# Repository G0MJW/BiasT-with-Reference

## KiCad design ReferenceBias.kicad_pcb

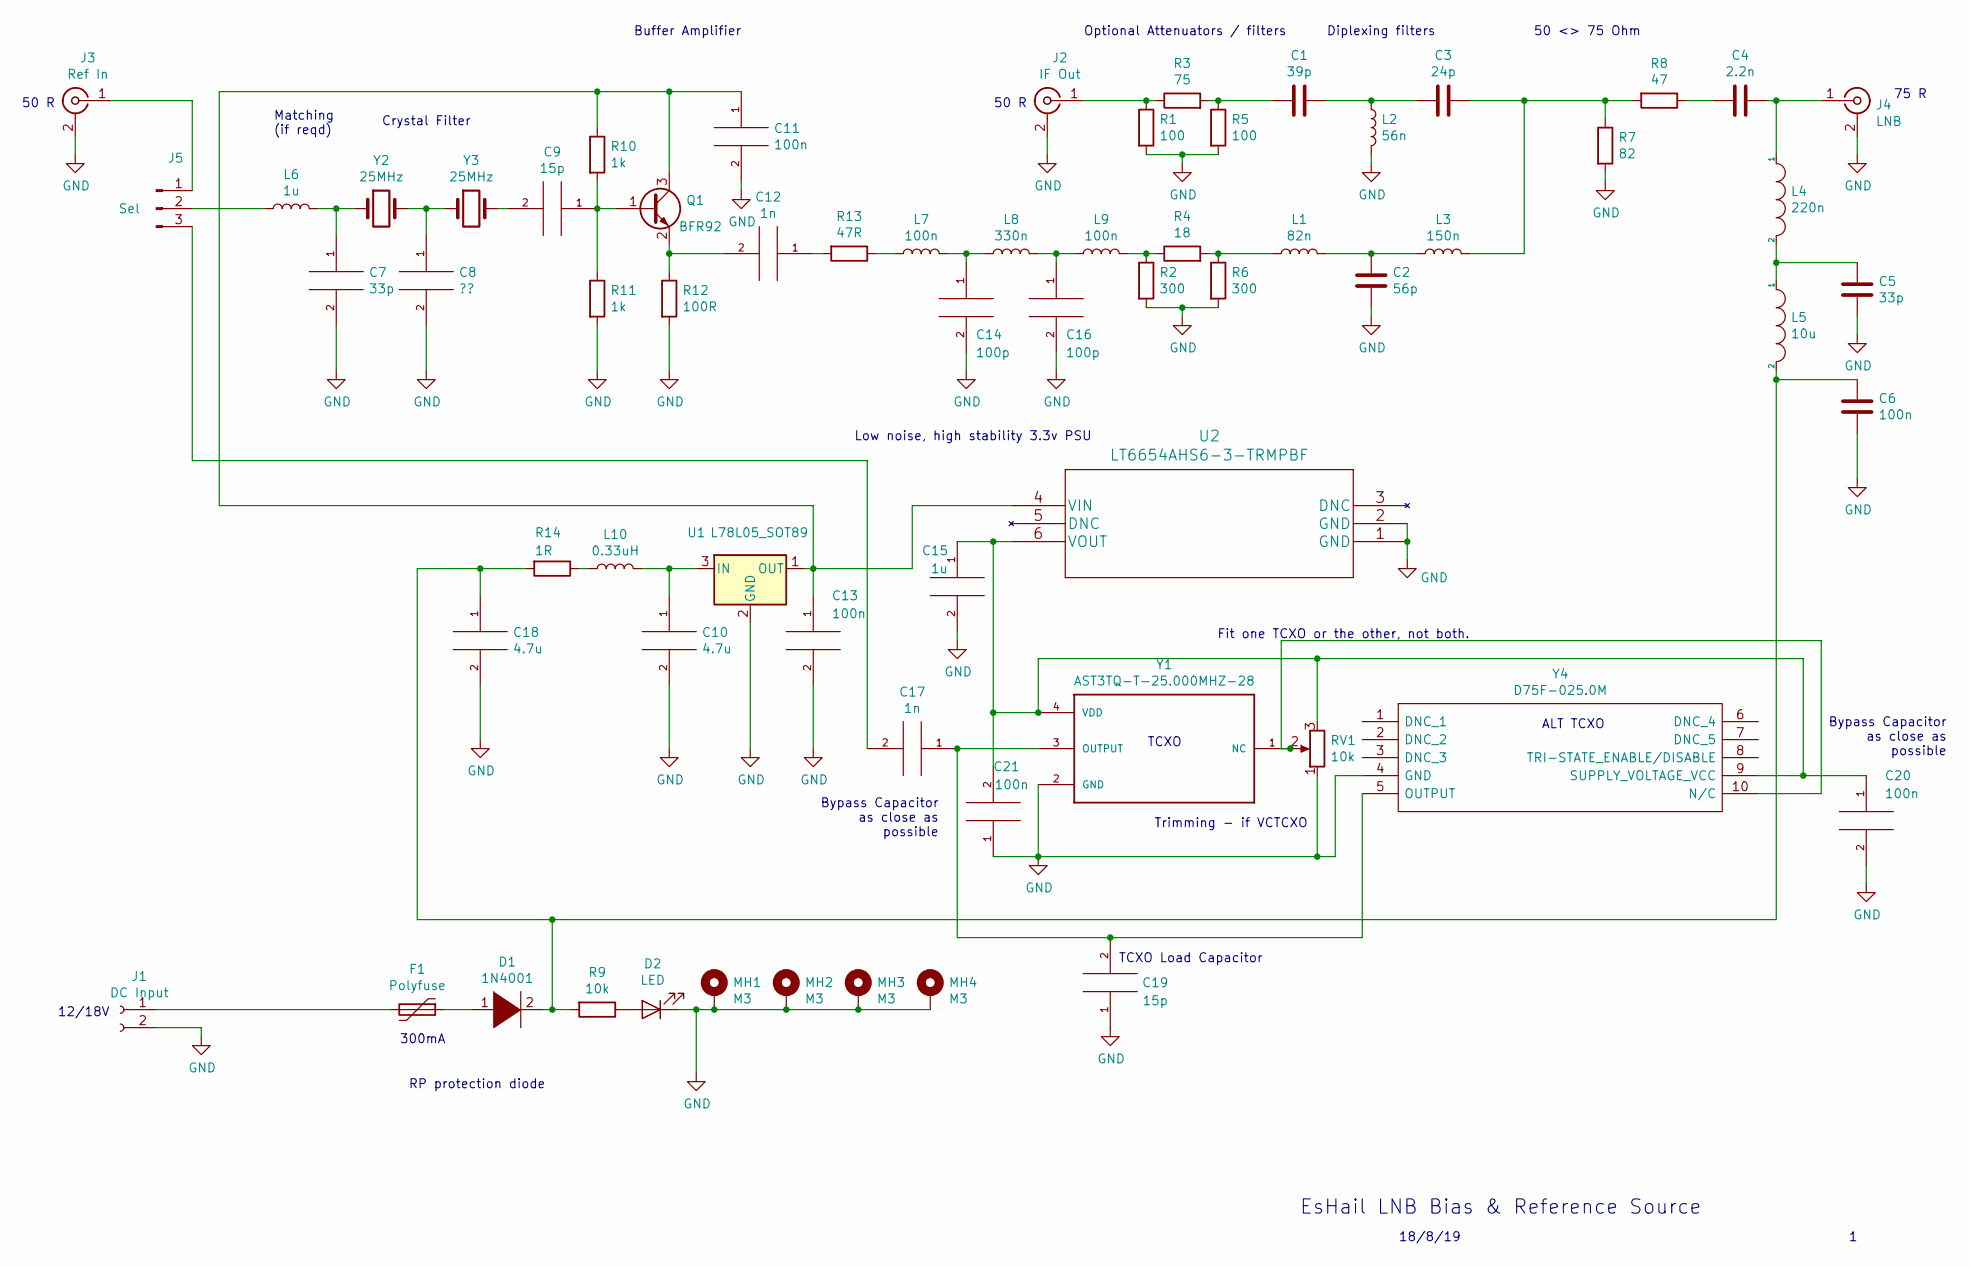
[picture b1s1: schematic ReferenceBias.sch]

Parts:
C1: 39p; C_0805_2012Metric_Pad1.15x1.40mm_HandSolder
C2: 56p; C_0805_2012Metric_Pad1.15x1.40mm_HandSolder
C3: 24p; C_0805_2012Metric_Pad1.15x1.40mm_HandSolder
C4: 2.2n; C_0805_2012Metric_Pad1.15x1.40mm_HandSolder
C5, C7: 33p; C_0805_2012Metric_Pad1.15x1.40mm_HandSolder
C6, C11: 100n; C_0805_2012Metric_Pad1.15x1.40mm_HandSolder
C8: ??; C_0805_2012Metric_Pad1.15x1.40mm_HandSolder
C9, C19: 15p; C_0805_2012Metric_Pad1.15x1.40mm_HandSolder
C10, C18: 4.7u; C_1206_3216Metric
C12, C17: 1n; C_0805_2012Metric_Pad1.15x1.40mm_HandSolder
C13: 100n; C_0805_2012Metric
C14, C16: 100p; C_0805_2012Metric_Pad1.15x1.40mm_HandSolder
C15: 1u; C_1210_3225Metric_Pad1.42x2.65mm_HandSolder
C20, C21: 100n; C_0603_1608Metric
D1: 1N4001; D_SOD-323_HandSoldering
D2: LED; LED_D3.0mm
F1: Polyfuse; Fuse_1210_3225Metric_Pad1.42x2.65mm_HandSolder
J1: DC Input; BarrelJack_Horizontal
J2: IF Out; SMA_Amphenol_132134-16_Vertical
J3: Ref In; SMA_Amphenol_132134-16_Vertical
J4: LNB; BNC_Dual_F_Connector
J5: Sel; PinHeader_1x03_P2.54mm_Vertical
L1: 82n; L_0805_With_Holes
L2: 56n; L_0805_With_Holes
L3: 150n; L_0805_With_Holes
L4: 220n; L_0805_With_Holes
L5: 10u; L_0805_With_Holes
L6: 1u; L_0805_With_Holes
L7, L9: 100n; L_0805_With_Holes
L8: 330n; L_0805_With_Holes
L10: 0.33uH; L_1210_3225Metric
MH1, MH2, MH3, MH4: M3; MountingHole_3.2mm_M3_DIN965
Q1: BFR92; SOT-323_SC-70
R1, R5: 100; R_0805_2012Metric
R2, R6: 300; R_0805_2012Metric
R3: 75; R_0805_2012Metric
R4: 18; R_0805_2012Metric
R7: 82; R_0805_2012Metric
R8: 47; R_0805_2012Metric
R9: 10k; R_0805_2012Metric
R10, R11: 1k; R_0805_2012Metric_Pad1.15x1.40mm_HandSolder
R12: 100R; R_0805_2012Metric_Pad1.15x1.40mm_HandSolder
R13: 47R; R_0805_2012Metric_Pad1.15x1.40mm_HandSolder
R14: 1R; R_0805_2012Metric
RV1: 10k; Potentiometer_Bourns_3269W_Vertical
U1: L78L05_SOT89; SOT-89-3
U2: LT6654AHS6-3-TRMPBF
Y1: AST3TQ-T-25.000MHZ-28; OSC_AST3TQ-T-25.000MHZ-28
Y2, Y3: 25MHz; Crystal_HC49-U_Vertical
Y4: D75F-025.0M; D75F0250M; Manufacturer_Part_Number D75F-025.0M

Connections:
GND: C2.1, C5.1, C6.1, C7.2, C8.2, C10.2, C11.2, C13.2, C14.2, C15.2, C16.2, C18.2, C19.1, C20.2, C21.1, D2.1 (K), J1.2, J2.2 (Ext), J3.2 (Ext), J4.2 (Ext), L2.2, MH1.1, MH2.1, MH3.1, MH4.1, R1.2, R2.2, R5.2, R6.2, R7.2, R11.2, R12.2, RV1.1, U1.2 (GND), U2.1 (GND), U2.2 (GND), Y1.2 (GND), Y4.4 (GND)
unnamed: C1.1, R3.2, R5.1
unnamed: C1.2, C3.1, L2.1
unnamed: C2.2, L1.2, L3.1
unnamed: C3.2, L3.2, R7.1, R8.2
unnamed: C4.1, J4.1 (In), L4.1
unnamed: C4.2, R8.1
unnamed: C5.2, L4.2, L5.1
unnamed: C7.1, L6.2, Y2.1
unnamed: C8.1, Y2.2, Y3.1
unnamed: C9.1, Q1.1 (B), R10.2, R11.1
unnamed: C9.2, Y3.2
unnamed: C10.1, L10.2, U1.3 (IN)
unnamed: C11.1, C13.1, Q1.3 (C), R10.1, U1.1 (OUT), U2.4 (VIN)
unnamed: C12.1, R13.2
unnamed: C12.2, Q1.2 (E), R12.1
unnamed: C14.1, L7.2, L8.1
unnamed: C15.1, C20.1, C21.2, RV1.3, U2.6 (VOUT), Y1.4 (VDD), Y4.9 (SUPPLY_VOLTAGE_VCC)
unnamed: C16.1, L8.2, L9.1
unnamed: C17.1, C19.2, Y1.3 (OUTPUT), Y4.5 (OUTPUT)
unnamed: C17.2, J5.3
unnamed: C6.2, C18.1, D1.2 (A), L5.2, R9.2, R14.2
unnamed: D1.1 (K), F1.1
unnamed: D2.2 (A), R9.1
unnamed: F1.2, J1.1
unnamed: J2.1 (In), R1.1, R3.1
unnamed: J3.1 (In), J5.1
unnamed: J5.2, L6.1
unnamed: L1.1, R4.2, R6.1
unnamed: L7.1, R13.1
unnamed: L9.2, R2.1, R4.1
unnamed: L10.1, R14.1
unnamed: RV1.2, Y1.1 (NC), Y4.10 (N/C)

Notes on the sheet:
EsHail LNB Bias & Reference Source
18/8/19
75 R
50 <> 75 Ohm
Optional Attenuators / filters
Diplexing filters
50 R
12/18V
RP protection diode
300mA
Crystal Filter
Matching (if reqd)
Buffer Amplifier
Low noise, high stability 3.3v PSU
TCXO
Trimming - if VCTCXO
ALT TCXO
Fit one TCXO or the other, not both.
TCXO Load Capacitor
Bypass Capacitor as close as possible

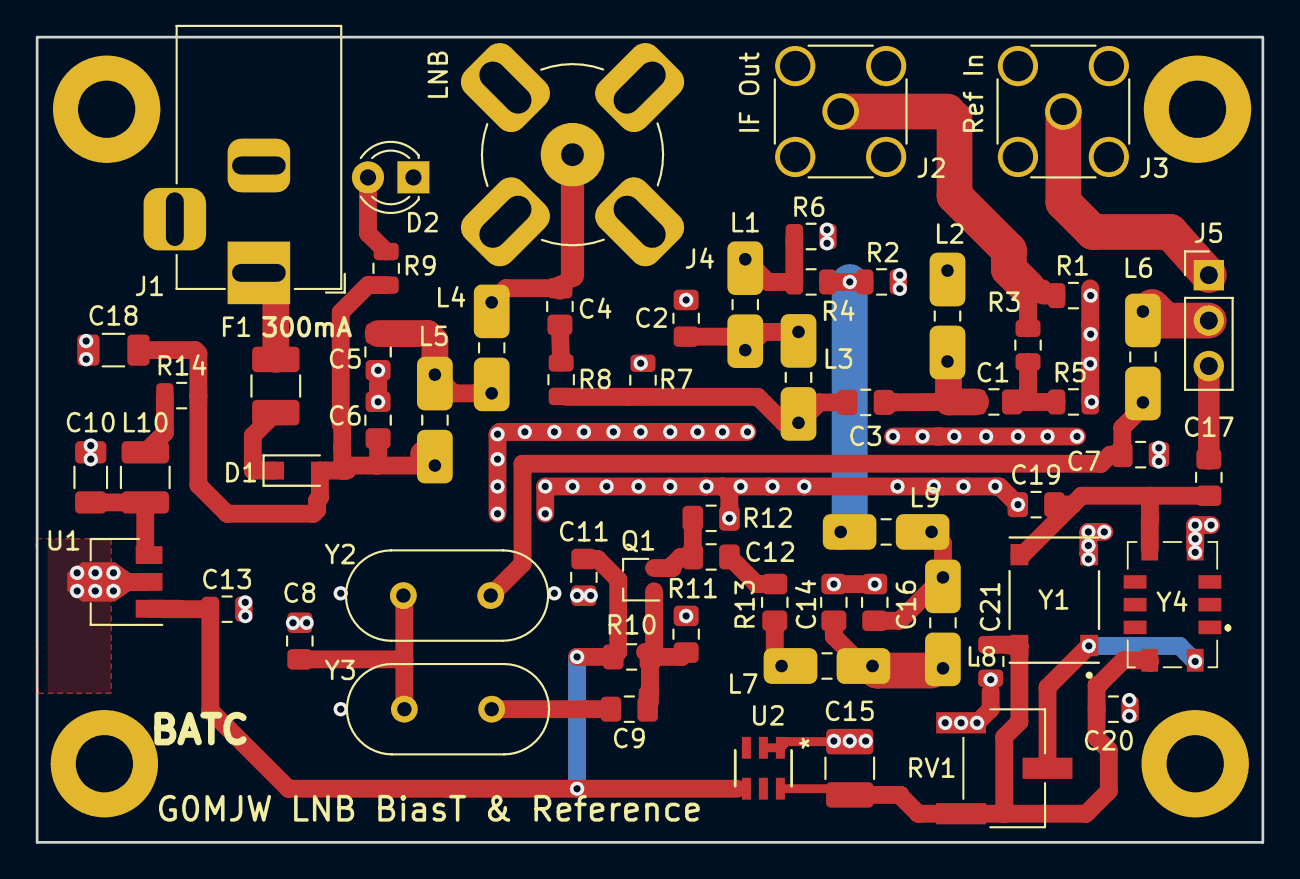
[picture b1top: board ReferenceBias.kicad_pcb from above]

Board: 2 copper layers, 68.5 x 45.0 mm, 65 parts (0 on the bottom side), 33 nets.

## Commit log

2019-08-20 3D Fix
2020-01-05 Update fp-info-cache

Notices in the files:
parts and their libraries:
Copyright 2016 Accelerated Designs. All rights reserved.
